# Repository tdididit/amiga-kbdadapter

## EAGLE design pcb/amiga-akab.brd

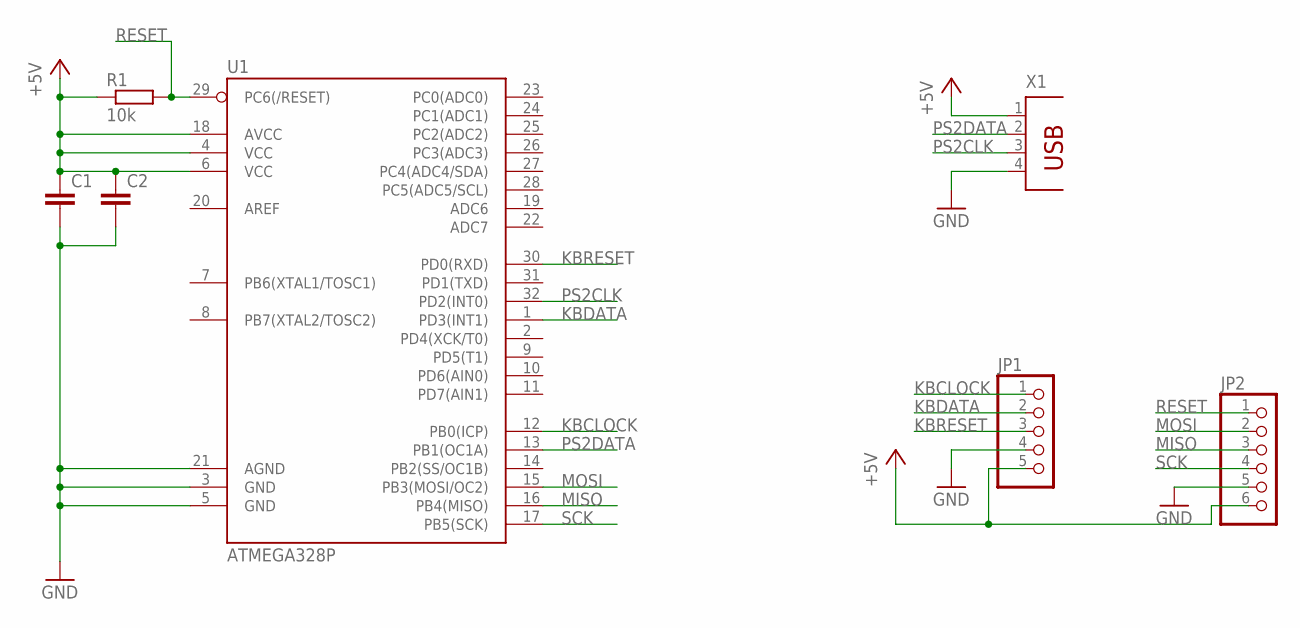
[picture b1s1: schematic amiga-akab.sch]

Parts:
C1, C2: C-EUC0603; C0603
JP1: HEADER-1X5ROUND; 1X05_ROUND
JP2: HEADER-1X6ROUND; 1X06_ROUND
R1: 10k; R0603
U1: ATMEGA328P; TQFP32-08
X1: PN87520

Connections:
+5V: C1.1, C2.1, JP1.5, JP2.6, R1.1, U1.4 (VCC), U1.6 (VCC), U1.18 (AVCC), X1.1
GND: C1.2, C2.2, JP1.4, JP2.5, U1.3 (GND), U1.5 (GND), U1.21 (AGND), X1.4
KBCLOCK: JP1.1, U1.12 (PB0(ICP))
KBDATA: JP1.2, U1.1 (PD3(INT1))
KBRESET: JP1.3, U1.30 (PD0(RXD))
MISO: JP2.3, U1.16 (PB4(MISO))
MOSI: JP2.2, U1.15 (PB3(MOSI/OC2))
PS2CLK: U1.32 (PD2(INT0)), X1.3
PS2DATA: U1.13 (PB1(OC1A)), X1.2
RESET: JP2.1, R1.2, U1.29 (PC6(/RESET))
SCK: JP2.4, U1.17 (PB5(SCK))

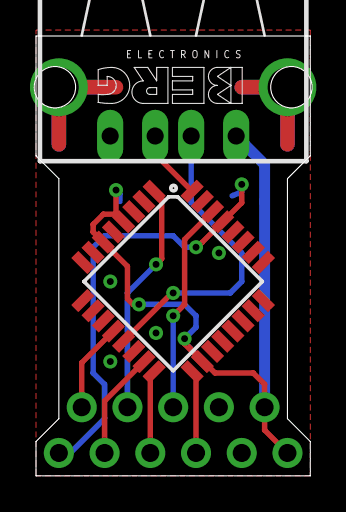
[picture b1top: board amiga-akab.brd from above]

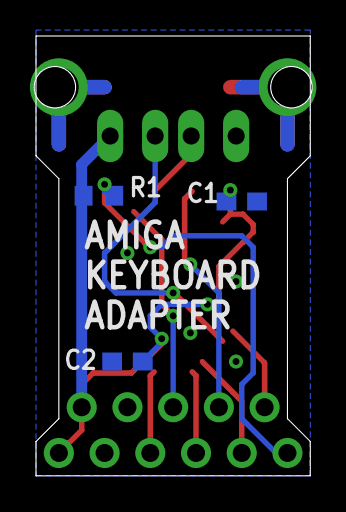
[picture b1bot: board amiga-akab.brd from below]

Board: 2 copper layers, 15.2 x 24.4 mm, 7 parts (3 on the bottom side), 11 nets.

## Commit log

2017-12-28 initial repository
    AKAB (Amiga Keyboard Adapter Board) is an AVR based PS/2 to Amiga keyboard adapter, released under GPLv3
    Merge branch 'release/v0.3-alpha'
    https://gitlab.com/hkzlab-retrocomputing/AKAB_Reloaded
2018-01-29 eagle & gerber files
2018-06-09 pcxtkbd
2018-06-09 update of readme

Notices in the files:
parts and their libraries:
SparkFun-IC-Microcontroller: Licensing: Creative Commons ShareAlike 4.0 International - https://creativecommons.org/licenses/by-sa/4.0
microbuilder: This work is placed in the public domain, and may be freely used for commercial and non-commercial work with the following conditions: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
